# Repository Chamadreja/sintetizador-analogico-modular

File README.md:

# Sintetizador Analógico Modular

Este proyecto consiste en el diseño y simulación de un sintetizador musical analógico basado en el estándar de síntesis sustractiva. Fue desarrollado para la materia **Laboratorio de Electrónica Analógica** en la UNRN (2023).

## Descripción General
El objetivo fue diseñar un sistema capaz de generar, filtrar y amplificar señales de audio mediante el control por tensión. El sistema es totalmente modular y opera con una fuente partida de ±12V.

## Módulos Implementados
Basado en el diseño técnico, el sintetizador cuenta con los siguientes bloques:

- **VCO (Voltage Controlled Oscillator):** Generador de señales básicas (Triangular, Cuadrada y Diente de Sierra) con control de frecuencia por tensión. Utiliza operacionales de alta velocidad (Serie TL08x/TL07x).
- **VCF (Voltage Controlled Filter):** Filtro pasa-bajos activo con control de frecuencia de corte, permitiendo el modelado del timbre sonoro.
- **VCA (Voltage Controlled Amplifier):** Etapa de salida que controla la amplitud de la señal mediante una tensión de control externa.
- **Generador de Envolvente (ADSR):** Control temporal del sonido en cuatro etapas: Attack, Decay, Sustain y Release.
- **LFO (Low Frequency Oscillator):** Oscilador de baja frecuencia para modulación de parámetros (vibrato/tremolo).
- **Mixer:** Etapa sumadora para combinar las distintas fuentes de señal antes del filtrado.

## Especificaciones Técnicas
- **Alimentación:** ±12V DC (Fuente partida diseñada con reguladores 7812/7912).
- **Componentes clave:** Amplificadores operacionales TL082/TL072, transistores de propósito general (BC547/557) y potenciómetros de precisión para el control manual.
- **Herramientas:** Diseñado y validado mediante simulaciones en **Proteus Professional**.

## Resultados y Simulación
En la carpeta `/simulaciones` se pueden observar las capturas del osciloscopio, donde se verifica:
1. La linealidad del VCO en el rango audible.
2. La respuesta en frecuencia del VCF.
3. El correcto funcionamiento del ciclo ADSR sobre el VCA.

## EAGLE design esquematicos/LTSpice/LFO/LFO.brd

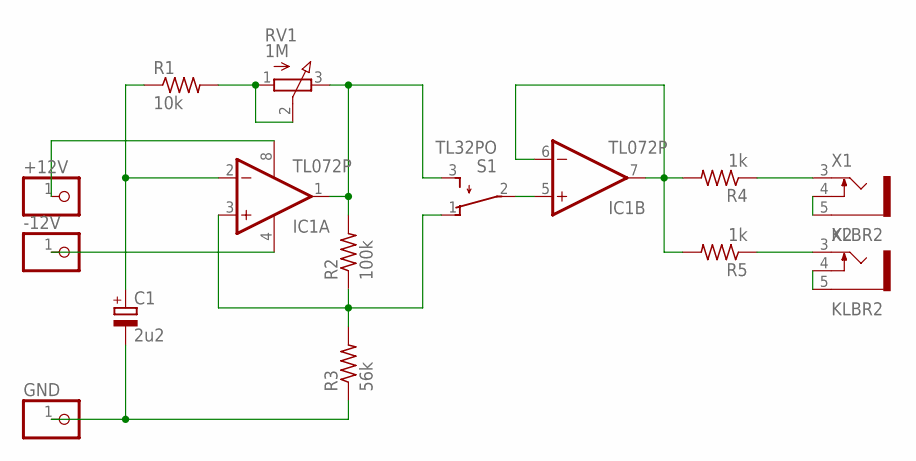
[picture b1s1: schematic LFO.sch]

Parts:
+12V: PINHD-1X1; 1X01
-12V: PINHD-1X1; 1X01
C1: 2u2; E2,5-6E
GND: PINHD-1X1; 1X01
IC1: TL072P; DIL08
R1: 10k; 0204/7
R2: 100k; 0204/7
R3: 56k; 0204/7
R4, R5: 1k; 0204/7
RV1: 1M; 3RP/1610N
S1: TL32PO; TL3XPO
X1, X2: KLBR2

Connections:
unnamed: R1.2, RV1.1 (A), RV1.2 (S)
unnamed: IC1.1 (OUT), R2.2, RV1.3 (E), S1.3 (S)
unnamed: IC1.3 (+IN), R2.1, R3.2, S1.1 (O)
unnamed: C1.+, IC1.2 (-IN), R1.1
unnamed: C1.-, GND.1, R3.1
unnamed: IC1.5 (+IN), S1.2
unnamed: IC1.6 (-IN), IC1.7 (OUT), R4.2, R5.2
unnamed: R5.1, X2.3
unnamed: X1.4, X1.5
unnamed: X2.4, X2.5
unnamed: R4.1, X1.3
unnamed: +12V.1, IC1.8 (V+)
unnamed: -12V.1, IC1.4 (V-)

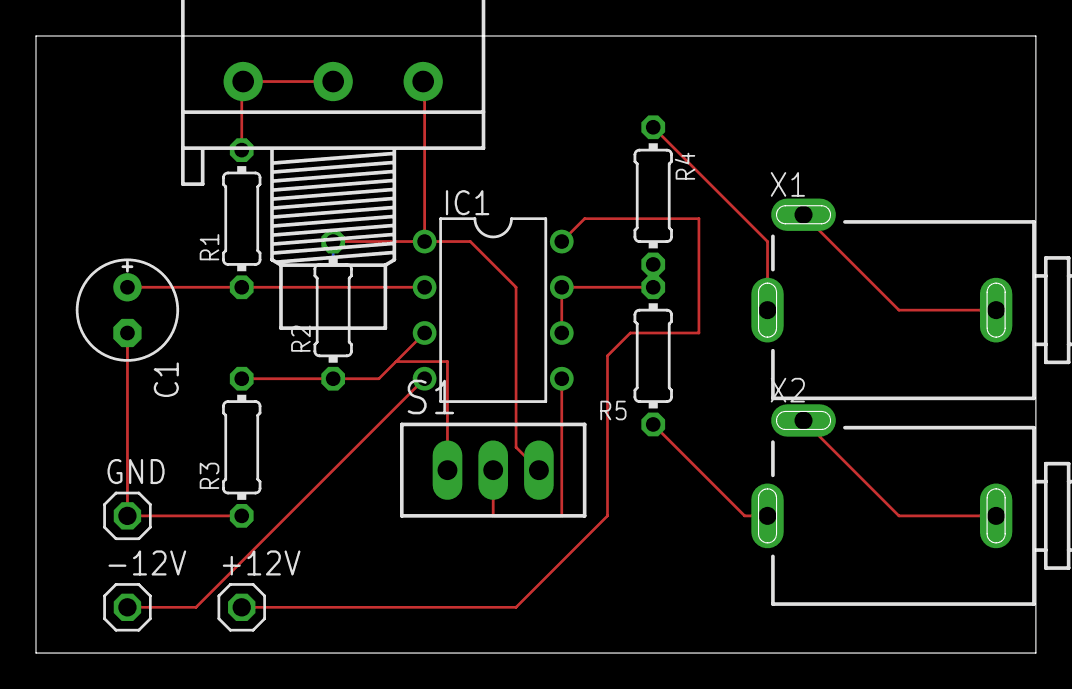
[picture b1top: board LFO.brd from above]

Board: 2 copper layers, 55.6 x 34.3 mm, 14 parts (0 on the bottom side), 13 nets.

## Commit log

2025-12-18 Subida de archivos
